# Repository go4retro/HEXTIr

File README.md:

# HEXTIr
TI HEX-BUS SD Drive Interface
Copyright (C) 2017-20  Jim Brain

## Description
Coupled with an Atmel ATMEGA328 microcontroller (either as a standalone PCB or an 
Arduino UNO, Nano, etc. development board), this firmware implements the functionality
of the various HEXBUS peripherals:

* Secure Digital (SD) based random access disk drive at device # 100
* RS232 port at device # 20
* RS232-based printer port at device #10
* RTC-based clock at device 230

## Implementation
### Arduino Implementation
Configure the Arduino IDE for the specific board in use. Adjust pin mappings in config.h
if the board does not use Arduino UNO mappings.  Once configured, load the 
src.ino file in the src directory, compile and download the object code to the Arduino
system.

Because the GCC C++ compiler and Arduino IDE settings compile the code slightly differently,
the resulting code size is larger and thus not all features can be enabled.  By default, 
only the driver function is enabled in the Arduino build.  You can optionally enable some
of the other peripherals by uncommenting lines in config.h:

```
#elif CONFIG_HARDWARE_VARIANT == 4
/* ---------- Hardware configuration: Old HEXTIr Arduino ---------- */

#define INCLUDE_DRIVE
//#define INCLUDE_CLOCK
//#define INCLUDE_SERIAL
//#define INCLUDE_PRINTER
```

The code has been successfully compiled using Arduino IDE 1.8.19 and 2.0.3.

### Native Implementation
The best code size is obtained by compiling the code natively via the AVR-GCC toolchain.

**To use the PCB design in the PCB directory, run the following make command:**

> make CONFIG=config clean all fuses program

**To use an Arduino UNO with a SD Card shield, run the following make command:**

> make CONFIG=config-arduino clean all fuses program

You may need to adjust the avrdude settings in the respecive config files in the 
main directory.

Native and Arduino builds differ only in the pin mappings.  All features are enabled
in both builds.  If space becomes an issue, you can comment out specific peripherals in config.h:

```
#define INCLUDE_DRIVE
#define INCLUDE_CLOCK
#define INCLUDE_SERIAL
#define INCLUDE_PRINTER
```

## PCB Design Copyright

This project's PCB files are free designs; you can redistribute them 
and/or modify them under the terms of the Creative Commons
Attribution-ShareAlike 4.0 International License.

You should have received a copy of the license along with this
work. If not, see <http://creativecommons.org/licenses/by-sa/4.0/>.

These files are distributed in the hope that they will be useful,
but WITHOUT ANY WARRANTY; without even the implied warranty of
MERCHANTABILITY or FITNESS FOR A PARTICULAR PURPOSE.  See the
license for more details.

## Firmware Copyright

This program is free software; you can redistribute it and/or modify
it under the terms of the GNU General Public License as published by
the Free Software Foundation; version 2 of the License only.

This program is distributed in the hope that it will be useful,
but WITHOUT ANY WARRANTY; without even the implied warranty of
MERCHANTABILITY or FITNESS FOR A PARTICULAR PURPOSE.  See the
GNU General Public License for more details.

You should have received a copy of the GNU General Public License
along with this program; if not, write to the Free Software
Foundation, Inc., 59 Temple Place, Suite 330, Boston, MA  02111-1307  USA

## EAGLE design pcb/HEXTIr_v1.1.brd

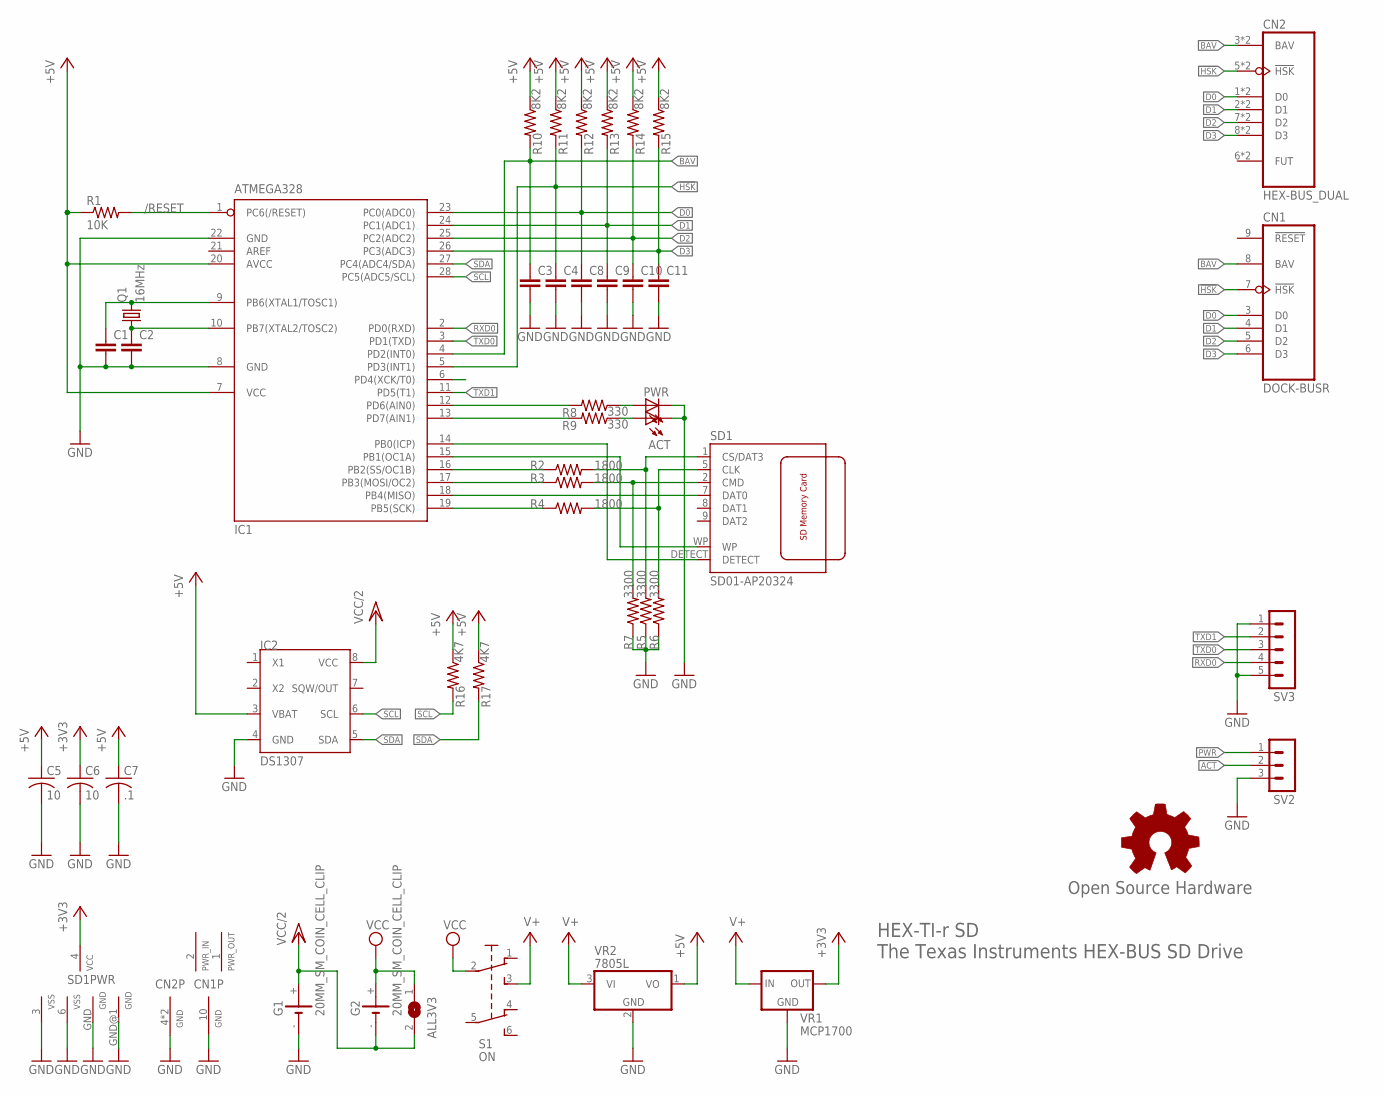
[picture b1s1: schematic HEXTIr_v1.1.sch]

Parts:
ACT: LED3MM
ALL3V3: SJ
C1, C2, C3, C4, C8, C9, C10, C11: C-EU025-024X044; C025-024X044
C5, C6: 10; C025-025X050
C7: .1; C025-025X050
CN1: DOCK-BUSR; DOCK-BUS-RP
CN2: HEX-BUS_DUAL
G1, G2: 20MM_SM_COIN_CELL_CLIP
GOLD_ORB_SM1: Open Source Hardware; OSHW_5MM
IC1: ATMEGA328; DIL28-3
IC2: DS1307; DIL08
PWR: LED3MM
Q1: 16MHz; HC49U-V
R1: 10K; 0204V
R2, R3, R4: 1800; 0204V
R5, R6, R7: 3300; 0204V
R8, R9: 330; 0204V
R10, R11, R12, R13, R14, R15: 8K2; 0204V
R16, R17: 4K7; 0204V
S1: ON; TINY-SLIDE
SD1: SD01-AP20324
SV2: MA03-1
SV3: MA05-1
VR1: MCP1700; TO92
VR2: 7805L; TO92

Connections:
!HSK: C4.1, CN1.7 (!HSK), CN2.5 (!HSK), CN2.5' (!HSK), IC1.5 (PD3(INT1)), R11.2
+3V3: C6.1, SD1.4 (3V3), VR1.3 (OUT)
+5V: C5.1, C7.1, IC1.7 (VCC), IC1.20 (AVCC), IC2.3 (VBAT), R1.1, R10.1, R11.1, R12.1, R13.1, R14.1, R15.1, R16.1, R17.1, VR2.1 (VO)
/RESET: IC1.1 (PC6(/RESET)), R1.2
ACT: IC1.13 (PD7(AIN1)), R9.2, SV2.2
B2: C1.1, IC1.9 (PB6(XTAL1/TOSC1)), Q1.2
B3: C2.1, IC1.10 (PB7(XTAL2/TOSC2)), Q1.1
BAV: C3.1, CN1.8 (BAV), CN2.3 (BAV), CN2.3' (BAV), IC1.4 (PD2(INT0)), R10.2
D0: C8.1, CN1.3 (D0), CN2.1 (D0), CN2.1' (D0), IC1.23 (PC0(ADC0)), R12.2
D1: C9.1, CN1.4 (D1), CN2.2 (D1), CN2.2' (D1), IC1.24 (PC1(ADC1)), R13.2
D2: C10.1, CN1.5 (D2), CN2.7 (D2), CN2.7' (D2), IC1.25 (PC2(ADC2)), R14.2
D3: C11.1, CN1.6 (D3), CN2.8 (D3), CN2.8' (D3), IC1.26 (PC3(ADC3)), R15.2
GND: ACT.K (C), C1.2, C2.2, C3.2, C4.2, C5.2, C6.2, C7.2, C8.2, C9.2, C10.2, C11.2, CN1.10 (GND), CN2.4 (GND), CN2.4' (GND), G1.-, IC1.8 (GND), IC1.22 (GND), IC2.4 (GND), PWR.K (C), R5.1, R6.1, R7.1, SD1.3 (VSS), SD1.6 (VSS), SD1.GND, SD1.GND@1 (GND), SV2.3, SV3.1, SV3.5, VR1.1 (GND), VR2.2 (GND)
MISO: IC1.18 (PB4(MISO)), SD1.7 (DAT0)
MOSI: IC1.17 (PB3(MOSI/OC2)), R3.1
unnamed: R2.2, R5.2, SD1.1 (CS/DAT3)
unnamed: R3.2, R7.2, SD1.2 (CMD)
unnamed: R4.2, R6.2, SD1.5 (CLK)
unnamed: IC1.15 (PB1(OC1A)), SD1.WP
unnamed: IC1.14 (PB0(ICP)), SD1.DETECT
unnamed: ACT.A, R9.1
unnamed: PWR.A, R8.1
PWN_IN: CN1.2 (PWN_IN)
PWR: IC1.12 (PD6(AIN0)), R8.2, SV2.1
PWR_OUT: CN1.1 (PWR_OUT)
RXD0: IC1.2 (PD0(RXD)), SV3.4
SCK: IC1.19 (PB5(SCK)), R4.1
SCL: IC1.28 (PC5(ADC5/SCL)), IC2.6 (SCL), R16.2
SDA: IC1.27 (PC4(ADC4/SDA)), IC2.5 (SDA), R17.2
SS: IC1.16 (PB2(SS/OC1B)), R2.1
TXD0: IC1.3 (PD1(TXD)), SV3.3
TXD1: IC1.11 (PD5(T1)), SV3.2
V+: S1.3 (S), VR1.2 (IN), VR2.3 (VI)
VCC: ALL3V3.1, G2.+, S1.2
VCC/2: ALL3V3.2, G1.+, G2.-, IC2.8 (VCC)

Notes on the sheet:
HEX-TI-r SD The Texas Instruments HEX-BUS SD Drive

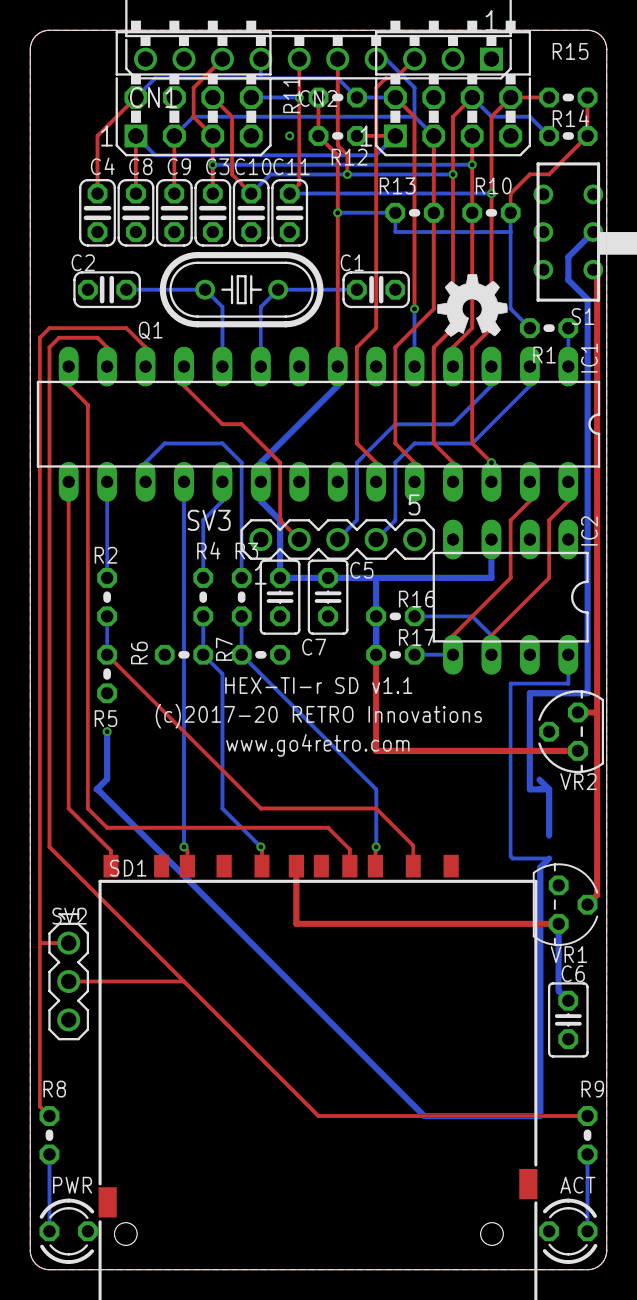
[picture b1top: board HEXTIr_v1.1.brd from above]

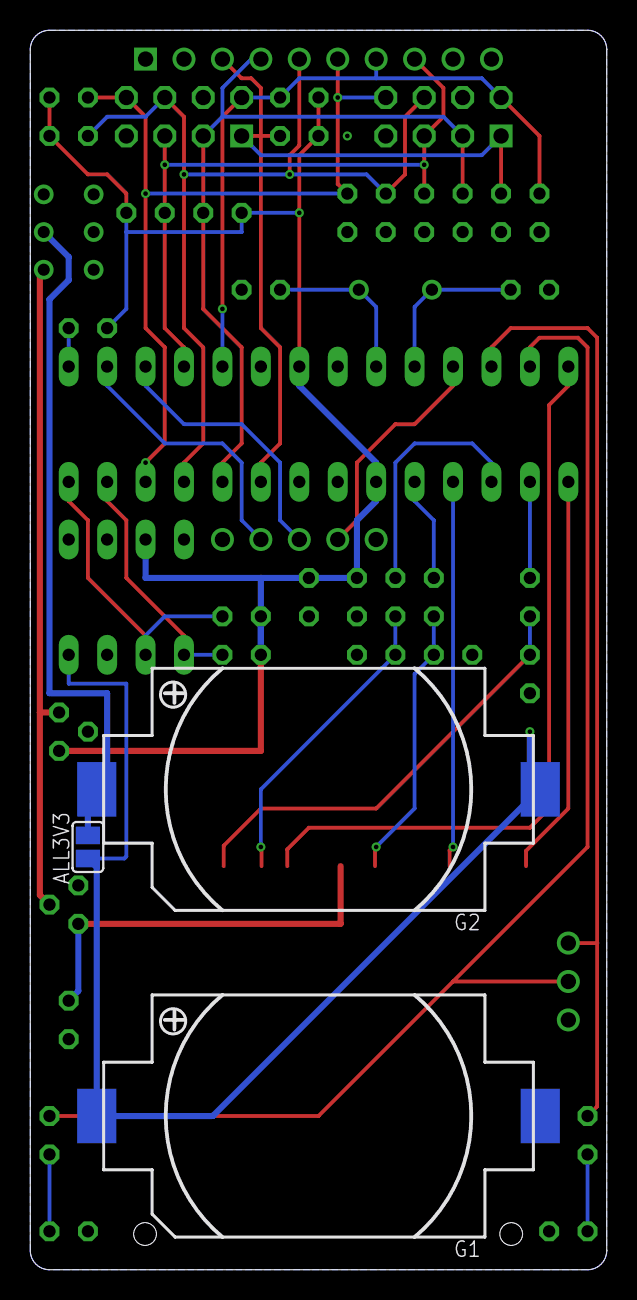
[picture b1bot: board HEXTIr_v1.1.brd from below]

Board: 2 copper layers, 38.1 x 81.9 mm, 45 parts (3 on the bottom side), 33 nets.

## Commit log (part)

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2017-10-28 Initial Push
2017-10-28 Clean up holdoff code
2017-10-28 Restructure code
2017-10-28 Remove glitch removal code (unneeded) and fix timing issue in hex_write
2017-10-28 Convert to Eclipse C Project
2017-10-28 Listen only on single device ID
2017-10-28 Refactor hex bus functions into separate source file
2017-10-28 More code cleanup
2017-10-29 Change device numbering from 100-115 to 100-107 and 108-117, to match device ID set in HexBus spec.
2017-10-29 Remove uIEC testing config
2017-10-29 Clean up flowerbox
2017-10-31 Switch to MEGA328 for development
2017-10-31 Added another dir
2017-12-17 Fixed device selection code
2017-12-17 Env changes
2018-07-02 Initial support for Arduino Uno dev board
2018-07-02 Ardunio Instructions
2020-04-10 Small bug fixes and document fix
2020-04-28 Include <stddef.h> in main.c to compile when CONFIG_UART_DEBUG=n.
2020-05-16 A bit of code cleanup and pics of Arduino SD Shield wiring
2020-05-22 Add avr nature to project. Enables upload from eclipse.
2020-05-31 Cleaned up some #ifdefs around ARDUINO, and massaged dir structure and INO filename so both will compile. Removed lost of included C files from sketch, and moved all sketch code to main.cpp. Also add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
2020-06-02 A bit more code re-org, and added some flowerboxes.
2020-06-02 activity led and power management update
    Ensure that the activity LED is not illuminated while we sleep between messages when power management is enabled. Also make sure variant 1 and 2 build without error.
2020-06-03 Initial commit on device configuration support
    Adding ability to program the device addresses for supported peripheral groups via a specific configuration address
2020-06-03 timer_check removal, cleanup hex_receive_opts, switch to hex_get_data unless a string is needed.
2020-06-03 Refactored power management into separate file. Added native power mamagement functionality.
2020-06-03 update to led power control
    Update to ensure led is not lit during sleep time
2020-06-03 more conflict resolution
    fixing additional configurations
2020-06-03 change to config variant 3
    variant 3 selected by default for my builds
2020-06-04 led sleep control
    mask led set with volatile sleep control mark for sleeping with led off
2020-06-04 Initial EEPROM storage routines
2020-06-05 initial configuration control for setting config
    initial ram based configuration set routine
2020-06-06 fix numerous save and old issues
    fix and repair save/old issues with the hex open, write, and also remove hex_get_opts and replace with hex_get_data. remove existing file if write-only open (create new file)
2020-06-06 Remove missing h file include
2020-06-06 Add initial Arduino version of read catalog
    Using std OPEN/INPUT, read contents of a directory. INPUT continues until EOF I/O error is returned.
2020-06-07 optimize config parsing code
    get rid of the role-your-own and use library functions. smaller code. add new interface for use by writing to eeprom when needed.
2020-06-07 refactor configuration design
    replace independent CC-40 and TI-74 implementations with a open/read/write/close model for configuring peripheral addresses.
2020-06-07 Update serial open to properly finish
    Add hex_finish to finish off the successful open of a serial peripheral
2020-06-09 Initial Drive Request Status
    Initial implementation of drive request status. Needs additional work.
2020-06-10 Integrate clock to SD file system
    Initial connection of RTC clock to allow timestamp for files written to SD card via SD library.
2020-06-10 Updates to RTC
    Fixes and updates to RTC routines now that I have a DS3231 to actually test against.
2020-06-11 Update RTC usage
    Implement working SD lib interface to RTC for timestamps when RTC present
2020-06-12 OLD-PGM version of the catalog. Fixed long and short file names.
2020-06-14 Comment added.
2020-06-15 Added volume label attribute (DIR,VOL,FIL).
2020-06-19 OPEN/INPUT variant of catalog added. Work in progress.
2020-06-19 Function for files to skip. Some refatcoring.
2020-06-20 Fixed BASIC example for OPEN/INPUT.
2020-06-20 Aligned some drive ops for FatFS library and cleaned up some build warnings.
2020-06-21 Fixed check for open readonly in hex_open_catalog. Updated some comments.
2020-06-21 Added a debug library to abstract out debug statements. Added a rudimentary multi-channel software TX only uart to handle print and debug. Enabled printer and serial support (needs testing) on non Ar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
2020-06-21 Fixed return of HEXSTAT_EOF error in case reading beyond EOF.
2020-06-22 Replaced use of snprintf with char assignments in cat_bytes_to_kb.
2020-06-24 PGM header and trailer NOT in PROGMEM. Caused touble.
2020-06-28 M5dk2n catalog (#6)
    * OPEN/INPUT variant of catalog added. Work in progress.
    * Bytes to KB function.
    * Function for files to skip. Some refatcoring.
    * Catalog OPEN/INPUT : Read until EOF. BASIC example updated. WIP
    * Fixed BASIC example for OPEN/INPUT.
    * Fixed TODO : Send back error on anything not OPENMODE_READ in hex_catalog_open.
2020-06-28 M5dk2n catalog (#7)
    * List PGM files in SD card root directory and run selected program.
    * OLD-PGM version of the catalog.
    * OLD-PGM version of the catalog. Some refactoring.
    * OLD-PGM version of the catalog. Fixed long and short file names.
    * OLD-PGM version of the catalog. Refactoring.
    * OPEN/INPUT variant added.
2020-06-30 Cleanup and work to enable text version of catalog
2020-07-01 Small cleanup for native build
2020-07-03 Few more fixes for Arduino, still having issue on PGM reads.
2020-07-05 Fixed some more wrongly placed ifdefs. Arduino dir completes now, but does not send the files.
2020-07-10 Format file size for catalog as bytes or kiB. (#8)
2020-07-11 M5dk2n cat format fsize (#9)
    * Format file size for catalog as bytes or kiB.
    * Bugfix in format_file_size : Use ltoa rather then itoa.
2020-07-12 Fixed catalog showing only top level directory. File name starts at buffer[3] on sreid_mods rather then at buffer[0] on main. (#10)
2020-07-14 Initialize and free pattern in reserve_lun and free_lun.
2020-07-15 M5dk2n sreid mods (#11)
    * M5dk2n catalog (#7)
    * List PGM files in SD card root directory and run selected program.
    * OLD-PGM version of the catalog.
    * OLD-PGM version of the catalog. Some refactoring.
    * OLD-PGM version of the catalog. Fixed long and short file names.
    * OLD-PGM version of the catalog. Refactoring.
2020-07-19 M5dk2n sreid mods (#12)
    * M5dk2n catalog (#7)
    * List PGM files in SD card root directory and run selected program.
    * OLD-PGM version of the catalog.
    * OLD-PGM version of the catalog. Some refactoring.
    * OLD-PGM version of the catalog. Fixed long and short file names.
    * OLD-PGM version of the catalog. Refactoring.
2020-07-23 Conditional compile on CLOCK code in case Arduino sketch wants to disable
2020-07-31 Input Issue, DISPLAY mode.
2020-08-01 Input Issue, ARDUINO path.
2020-08-05 Input Issue, DISPLAY mode, add SPACE as delimiter.
2020-08-06 Input Issue. Test program TESTWR.PGM.
2020-08-18 Bugfix : Set BUFFSIZE 255 in src/config.h (256 was too large, caused problems).
2020-08-19 Input Issue : Corrected buffer size to 255.
2020-08-24 Enabled conditional serial debugging from Arduino IDE and temporarily fixed BUFSIZE issue with Arduino IDE build.
2020-08-24 second part of commit
2020-08-26 Merged SD and Fat libraries.
2020-08-28 Move serial init up to before rtc init()
2020-08-29 More cleanup, and added some debugging for clock.cpp
2020-08-31 Off-by-one month fix and proper DISPLAY file handling by Peter Engels
2020-09-01 Trim leading and trailing whitespaces from filename.
2020-09-01 Release 0.9.1.1
2020-09-01 Remove dependency for strlen in drive.cpp
2020-09-04 Bug fix for writing files > BUFSIZE, fix HW version 1 compile and enable bootloader.
2020-09-08 Peter Engels file support additions
2020-09-10 updated working cc40 test apps, corrected operation on writing past end of file.
2020-09-11 Remove a few dependencies and fix open flags.
2020-09-16 added support for data files in DISPLAY and INTERNAL mode. INTERNAL files may be RELATIVE. Added a special LUN 255 for reading, writing and verifying RAM/ROM images. Fixed the SYNTAX ERROR issue on R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
2020-09-16 Support for Special LUN=255 for binary file dumps (#20)
    * Add in alpha support for disk change detection.
    * Fixe issue of truncating files on APPEND of UPDATE
    * added more BASIC examples
    * added support for data files in DISPLAY and INTERNAL mode. INTERNAL files may be RELATIVE. Added a special LUN 255 for reading, writing and verifying RAM/ROM images. Fixed the SYNTAX ERROR issue on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
2020-09-20 Moved cd, md from OPEN to PRINT. New usage: OPEN #1,"100" PRINT #1,"md /jim" CLOSE #1
2020-09-23 Added support for renaming files and directories, multiple commands in a print statement, see doc/handling_directories.txt
2020-09-25 Hide more files if INCLUDE_* options disabled
2020-09-26 Make command dispatch system configurable (new or old)
2020-09-26 Switch commands to accept PAB struct by reference
2020-09-26 SWitch HEXBus cmd functions to return void
2020-09-26 More cleanup
2020-09-27 One final code fix, if USE_NEW_REGISTER is off
2020-09-27 Regression fixes, parser refactor some parser code
    * call drv_start in all drv functions that can be called directly (open,
    reset, restore, delete)
    * make parse_number work for clock and general number parsing
    * don't need buf2 out of parse_equate
    * send back correct errors on rename
    * switch parms for rename back ot original.
2020-09-28 General code cleanup and refactoring
    * No need for PSTR() in debug_puts_p now
    * Handle printer open options
    * Missing option in serial.cpp
    * All use common hex_send_size_response() now.
2020-09-28 More parser cleanup (default setings for serial and printer)
2020-09-28 Parse cmds on open #255 only if string > ""
2020-09-28 General drive.cpp code cleanup and refactoring FRESULT->HEXSTATUS
2020-09-29 Working EEPROM configuration capability
2020-09-29 return correct error on open when LUN=255 and BUF>255
2020-09-30 Simple version read: open #255, "100" : input #255, a$ : ? a$
2020-10-01 BUgfixes (0.9.2.1)
    * don't error out on serial open if already open, as per manual
    * serial was locked at 57600bps. Fixed
    * stop parsing cmds/options on first error
2020-10-02 Make drive functionality optional, for secondary devices
2020-10-02 premerge step
2020-10-02 Bump Version to 0.9.3.0
2020-10-03 Create Arduino-compatible PCB layout
2020-10-06 Revert "Merge in Peter Engels' update"
2020-10-06 workaround for writing data on LUN 0 with missing INTERNAL attribute.
2020-10-07 Bumper version to 0.9.3.1
2020-10-16 Fixed file handling of DISPLAY,RELATIVE files
2020-10-17 Added examples for use use of DISPLAY,RELATIVE
2020-10-17 Workaround for cumulative CRLF behind saved programs
2020-10-18 DISPLAY,RELATIVE was broken. Fixed.
2020-10-19 Fix to avoid added CRLF on saving program files. Removed the code to adjust filesize.
2020-10-22 Handle DISPLAY mode on LUN 0 (#29)
    * Added examples for use use of DISPLAY,RELATIVE
    * Switched back to DISPLAY mode at LUN 0
    * Workaround for cumulative CRLF behind saved programs
    * VERIFY needs the same workaround, therefore i moved from drv_read to drv_open
    * DISPLAY,RELATIVE was broken. Fixed.
    * EOF in DISPLAY,RELATIVE was broken too, Fixed again.
2020-12-05 fix for reading behind EOF
2020-12-08 fix for EOF on reading a file in internal mode, which it is saved in display mode
2020-12-18 Updated RWRAM
2020-12-21 Fixed cat_write_txt
2020-12-23 Small fix in clk_close
2020-12-24 CLean up files for merge
2020-12-30 cat_max_file_length_txt returns a too small buffersize, therefore you might get an error 12 with long filenames
2023-01-17 Updated Arduino pin mappings, fixed license file, clean up some warnings
2023-01-17 Refresh v1 PCB binaries
2023-01-17 A bit of README.md cleanup
2023-01-17 Compiled on Arduino IDE 1.8.19 and 2.0.3
2023-03-07 Updates to tone down aggressive power management
2023-07-06 Modify pin settings for base config to PCB v1.1
2024-06-11 Fixed English weekdays #36

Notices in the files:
pcb/HEXTIr_v1.1.brd:
(c)2017-20 RETRO Innovations
